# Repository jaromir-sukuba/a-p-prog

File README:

repository for https://hackaday.io/project/8559-pic16f1xxx-arduino-based-programmer
HW design files in cadsoft eagle 6 and higher

The whole project is licensed under MIT license, see LICENSE.md file.

https://cloud.githubusercontent.com/assets/6984904/17289293/5cedd6c0-57d9-11e6-86b8-8d692eaa24e3.JPG

image test

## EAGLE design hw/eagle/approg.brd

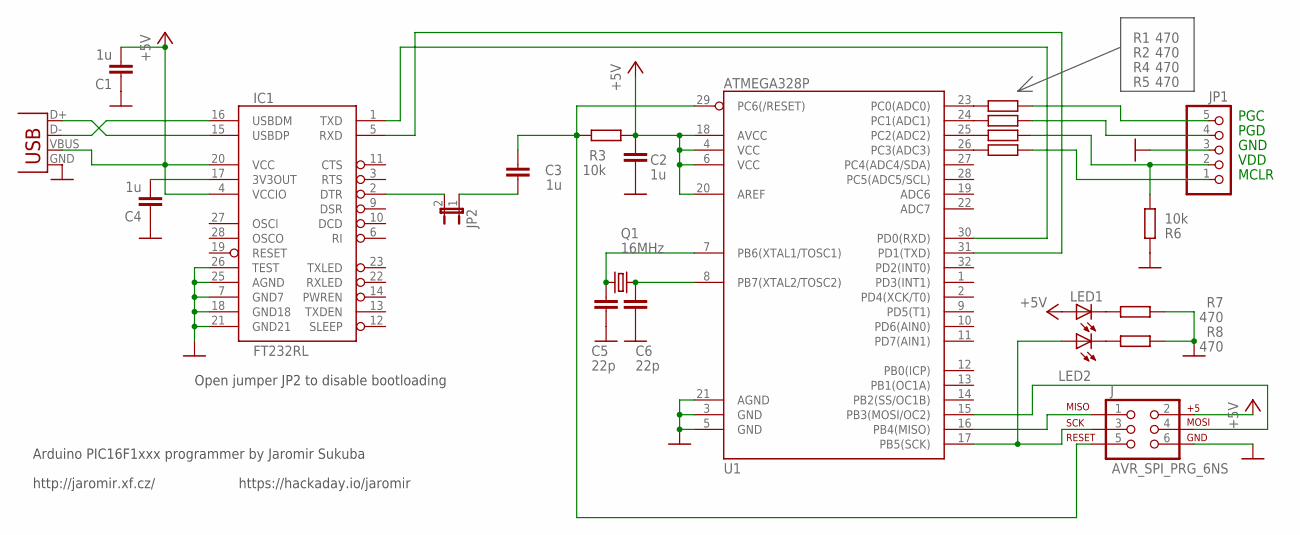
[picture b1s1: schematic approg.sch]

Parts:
C1, C2, C3, C4: 1u; R0805
C5, C6: 22p; R0805
IC1: FT232RL; SSOP28DB
J: AVR_SPI_PRG_6NS; 2X3-NS
JP1: PINHD-1X5/90; 1X05/90
JP2: JP1E; JP1
LED1, LED2: LEDCHIPLED_0805; CHIPLED_0805
Q1: 16MHz; HC49/S
R1, R2, R4, R5, R7, R8: 470; R0805
R3, R6: 10k; R0805
U1: ATMEGA328P; TQFP32-08
X1: USB-MICROB

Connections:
3V3: C4.2, IC1.17 (3V3OUT)
+5V: C1.2, C2.1, IC1.4 (VCCIO), IC1.20 (VCC), J.2, LED1.A, R3.1, U1.4 (VCC), U1.6 (VCC), U1.18 (AVCC), U1.20 (AREF), X1.VBUS
GND: C1.1, C2.2, C4.1, C5.2, C6.2, IC1.7 (GND7), IC1.18 (GND18), IC1.21 (GND21), IC1.25 (AGND), IC1.26 (TEST), J.6, JP1.3, R6.2, R7.1, R8.1, U1.3 (GND), U1.5 (GND), U1.21 (AGND), X1.GND
unnamed: IC1.2 (DTR), JP2.2
unnamed: C5.1, Q1.1, U1.7 (PB6(XTAL1/TOSC1))
unnamed: C6.1, Q1.2, U1.8 (PB7(XTAL2/TOSC2))
unnamed: C3.2, JP2.1
unnamed: C3.1, J.5, R3.2, U1.29 (PC6(/RESET))
unnamed: JP1.1, R5.1
unnamed: IC1.16 (USBDM), X1.D-
unnamed: J.1, U1.16 (PB4(MISO))
unnamed: J.4, U1.15 (PB3(MOSI/OC2))
unnamed: LED2.C, R8.2
unnamed: LED1.C, R7.2
unnamed: J.3, LED2.A, U1.17 (PB5(SCK))
unnamed: JP1.5, R1.1
unnamed: JP1.4, R2.1
unnamed: JP1.2, R4.1, R6.1
unnamed: R1.2, U1.23 (PC0(ADC0))
unnamed: R2.2, U1.24 (PC1(ADC1))
unnamed: R4.2, U1.25 (PC2(ADC2))
unnamed: R5.2, U1.26 (PC3(ADC3))
unnamed: IC1.15 (USBDP), X1.D+
U_RX: IC1.5 (RXD), U1.31 (PD1(TXD))
U_TX: IC1.1 (TXD), U1.30 (PD0(RXD))

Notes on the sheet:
MCLR
VDD
GND
PGD
PGC
Open jumper JP2 to disable bootloading
Arduino PIC16F1xxx programmer by Jaromir Sukuba
http://jaromir.xf.cz/
https://hackaday.io/jaromir

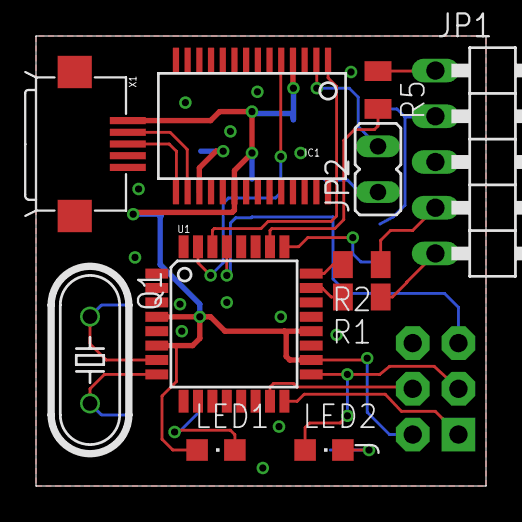
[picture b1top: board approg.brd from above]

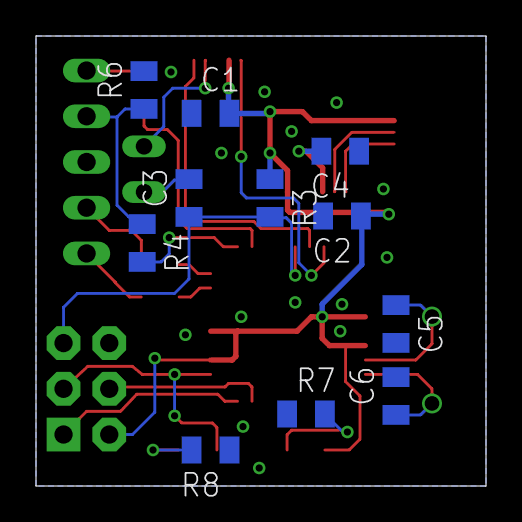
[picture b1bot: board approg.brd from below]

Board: 2 copper layers, 25.0 x 25.0 mm, 23 parts (11 on the bottom side), 25 nets.

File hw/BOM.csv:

Qty,Value,Device,Package,Parts,Description,PROD_ID,VALUE
1,,JP1E,JP1,JP2,JUMPER,,
2,,LEDCHIPLED_0805,CHIPLED_0805,LED1, LED2,LED,,
1,,PINHD-1X5/90,1X05/90,JP1,PIN HEADER,,
2,10k,R_0805,R0805,R3, R6,,,
1,16MHz,CRYSTALHC49S,HC49/S,Q1,CRYSTAL,,
4,1u,C_0806,R0805,C1, C2, C3, C4,,,
2,22p,C_0806,R0805,C5, C6,,,
6,470,R_0805,R0805,R1, R2, R4, R5, R7, R8,,,
1,ATMEGA328P,ATMEGA328_SMT,TQFP32-08,U1,32-Pin Atmega328 part,IC-09069,ATMEGA328P
1,AVR_SPI_PRG_6NS,AVR_SPI_PRG_6NS,2X3-NS,J,AVR ISP 6 Pin,,
1,FT232RL,FT232RLSSOP,SSOP28DB,IC1,USB UART,,
1,USB-MICROB,USB-MICROB,USB-MICROB,X1,USB Connectors,,

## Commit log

2015-11-24 :space_invader: Added .gitattributes & .gitignore files
2015-11-24 hw/sw revision 1, somehow dirty job
2015-12-01 gerber data
    gerber data
2015-12-02 files cleanup
    files cleanup
2015-12-23 BOM update
    BOM update
2015-12-23 parts support
    16F182x parts added
2016-01-07 MIT licensing update
    MIT licensing update
2016-04-01 support for PIC18
    support for PIC18
2016-07-26 PIC16 and PIC18 united
    and a lot of bugs fixed, PIC12F1xxx support
2016-07-26 minor fixes
2016-07-29 New devices supproted
2016-07-30 new devices, bugfixes
2016-08-01 readme
2016-08-01 readme update
2016-08-05 device support update
2016-08-16 device support
    new PIC16F1, new PIC18FJ family
2016-08-16 typos fixing
2016-09-05 version 0.9
    a lot of devices added, bugfixes
2016-09-06 ver 0.91
    programming speed improvement, part support
2016-09-09 ver 0.92
    massive rework of MCU selection, added MCU database, 67 new devices
    added
2016-09-09 changelog
2016-09-12 0.93
    bugfixes
2016-09-14 ver 0.94
    new devices, bugfixes
2016-09-16 ver 0.95
2018-06-17 ver 0.96
2018-06-18 ver 0.97
2018-06-19 ver 0.98
2018-06-28 ver 0.99
2018-11-07 rough schematic for project
2020-04-23 Fixed PIC16F1619 device ID typo and confirmed working
2021-04-22 Corrected inverted 18f47q10 / 18f27q10 signatures
    They were swapped see page 38 of https://ww1.microchip.com/downloads/en/DeviceDoc/PIC18F27-47Q10-Data-Sheet-40002043E.pdf
2021-04-26 Added preprocessor directive for mac. Fixes #20
2022-06-16 cli should exit immediately if dat file not found, otherwise it will cause a lot of issues, for example, report deviceID as 0x0000, segfault when it can not find correct flashsize and treat it as zer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
2022-06-16 add 16f1823 to device database, verified
2022-06-16 add global device database file for linux
2022-06-16 add Makefile for linux, support 'make install' to install device database to /etc/pp3/
2022-06-16 set a proper init value for sleep time
2022-06-16 add a help msg, and try to make it robust.
2022-06-16 add 16lf1823 to device database
2022-06-16 change readme.md, 1823/1825 verified
2022-06-17 new line in error msg
2022-06-17 Add Makefile.linux for pp firmware, it's very convenient to upload sketch with arduino-cli.
2022-09-06 Use correct logical operators instead of bitwise operators in conditions

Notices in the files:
parts and their libraries:
SparkFun-DigitalIC: Licensing: CC v3.0 Share-Alike You are welcome to use this library for commercial purposes.
